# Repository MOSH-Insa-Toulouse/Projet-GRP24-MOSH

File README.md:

# Projet Capteur Graphite GRP24

Ce Git contient les ressources nécessaire pour le projet 2021 qui s'inscrit dans l'UF *"Du capteur au banc de Test"* de l'INSA de Toulouse, 4ème année de Génie Physique.

## Sommaire

---

- [Livrables](##Livrables)
- [Description](##Description)
- [Arduino](##Arduino)
  - [Bibliothèques](###Bibliotèques)
  - [Notre code Arduino](###Notre-Code-Arduino)
- [KICAD](##Projet-KICAD)
  - [Placement des composants](###Placement-des-composants)
  - [Sockets KICAD pour les différents composants](###Sockets-KICAD-pour-les-différents-composants)
- [Application Android apk](##Application-Android-apk)
  - [MIT App Inventor](###MIT-App-Inventor)
  - [Notre application](###Notre-Application)
- [Banc de test](##Banc-de-test)
- [Pistes de réflexion](##Pistes-de-réflexion)
- [Information sur les auteurs](##Information-sur-les-auteurs)

## Livrables

---

- Shield PCB
- Code Arduino permettant la mesure de la resistance R et la tension, ainsi que le contrôle des fonctionnalités BT, OLED et capteur rotatoire
- Application android APK réalisée avec MIT APP INVENTOR
- Datasheet du capteur de déformation

## Description

---
Dans le cadre de l'UF MOSH, nous avons conçu un capteur résistif composé de matériaux peu chers, en effet, un simple papier et un crayon nous permettent de créer ce capteur.
Ici, le phénomène physique est l'effet tunnel, en effet, il existe un lien entre la conduction des électrons et la distance interatopique du réseau percolet.
En faisant varier la distance séparant les particules du réeau (en pliant une feuille de papier sur laquelle on aura déposé du graphite par exemple), la conductivité du graphite varie, la résistivité varier également, et donc, la résistance variera aussi en fonction des dimensions du capteur, c'est cette propriété que l'on va exmploiter avec de créer notre capteur résistif. Nous avons également implémenté  un shield sur notre chaine de mesures, ce dernier a été conçu a l'aide du logiciel KICAD et aura un rôle de conditionneur du signal; le shield est composé d'un module Bluetooth, un écran OLED, un encodeur rotatoire,  un amplificateur transimpédance ainsi qu'une entrée analogique pour le capteur résistif; pour finir, nous avons effectué l'ensemble des tests du circuit sur le logiciel LTSpice.

Nous avons ensuite imprimé notre circuit PCB après validation de l'équipe pedagogique, on a utilisé une carte Arduino pour la lecture des mesures et la création des fonctions relatives à l'écran OLED, au module Bluetooth ainsi qu'a l'encodeur rotatoire même si on n'a pas fini de coder cette partie; avec le site MIT App Inventor, nous avons développé une application Android qui a pour but d'envoyer et de recevoir des donnérs via Bluetooth.
Pour tester notre capteur, nous avons utilisé différents types de crayons (B, HB, 2H), nous avons utilité le banc de test mis a disposition en salle d'instrumentation comportant 7 bosses de rayon de courbure différent, les mesures ont été lues directement sur l'écran OLED.

### Code Arduino

Le code Arduino permet d'afficher les valeurs de tension dans la console ainsi que les valeurs de résistance, nous avons implémenté dans le code arduino le calcul de résistance qui été déjà présent dans l'APK android, le code nous fourni également la valeur de tension lue en sortie du circuit transimpédance, il écrit également la valeur de résistance sur l'écran OLED

### KICAD

Sur le logiciel KICAD on a créé les modèles pour l'écran OLED, le module Bluetooth ainsi que l'encodeur rotatoire, il y a également une interface de notre capteur résistif en graphite.

### Application apk

L'application android permet de lire la valeur de tension, elle calcule également la résistance du capteur en connaissance toutes les valeurs des résistances du circuit transimpédance, elle dessine une courbe représentant la variation de tension sur toute la durée d'utilisation du capteur.

## Arduino
---
En résumé, notre code Arduino permet la mesure d'une tension en sortie du circuit transimpédance, d'envoyer la mesure de cette tension par Bluetooth, le code permet le calcul de la résistancede notre capteur résistif, il envoie également cette valeur par Bluetooth, il affiche la valeur de tension dans la console ainsi que la valeur de résistance sur l'écran OLED, n'ayant pas fini le code de l'encodeur rotatoire, toutes les mesures ont été réalisées sans celui-ci.

### Bibliotèques

- Installer la bibliothèque ["Adafruit GFX Library"](https://github.com/MOSH-Insa-Toulouse/Projet-GRP24-MOSH/blob/main/Libraries%20ajout%C3%A9es/Adafruit-GFX-Library-master.zip)
- Installer la bibliothèque ["Adafruit SSD1306"](https://github.com/MOSH-Insa-Toulouse/Projet-GRP24-MOSH/blob/main/Libraries%20ajout%C3%A9es/Adafruit_SSD1306-master.zip)
- Installer la bibliothèque ["Adafruit BusIOa"](https://github.com/MOSH-Insa-Toulouse/Projet-GRP24-MOSH/blob/main/Libraries%20ajout%C3%A9es/Adafruit_BusIO-master.zip)

### Notre code arduino

Notre code Arduino permet de:

- Mesure la tension de sortie du circuit transimpédance
- Calcule la résistance du capteur de graphite connaissant la fonction de transfert du conditionneur
- Envoie la mesure de la tension et de la resistance via Bluetooth sur 1 octet
- Affiche les mesures de tension, de résistance et possède un menu pour choisir entre un offset et un gain numérique sur un écran OLED
- Gère l'encodeur rotatoire

[_Pour télécharger le code_](https://github.com/MOSH-Insa-Toulouse/Projet-GRP24-MOSH/blob/main/code/code_avec_encodeur_et_gain_non_fini.ino)

[_Pour télécharger la version pour les mesures(sans encodeur rotatoire)_](https://github.com/MOSH-Insa-Toulouse/Projet-GRP24-MOSH/blob/main/code/code_banc_test.ino)

```C++
//connexion BT
#include <SoftwareSerial.h>
#define rxPin 10 //cable jaune sur Tx
#define txPin 11 //cable vert sur Rx
#define baudrate 9600
SoftwareSerial mySerial(rxPin,txPin);

volatile byte RX = 0;
byte serialRX;
byte serialTX;
int action=0;

//OLED (définition)
#include <Adafruit_BusIO_Register.h>
#include <Adafruit_I2CDevice.h>
#include <Adafruit_I2CRegister.h>
#include <Adafruit_SPIDevice.h>

#include <Adafruit_SSD1306.h>
#include <Adafruit_GFX.h>
#include <SPI.h>
#include <Wire.h>

#define oled Adafruit_SSD1306
#define SCREEN_WIDTH 128 // OLED display width, in pixels
#define SCREEN_HEIGHT 32 // OLED display height, in pixels
#define OLED_RESET     4 // Reset pin # (or -1 if sharing Arduino reset pin)

#define SCREEN_ADDRESS 0x3C ///< See datasheet for Address; 0x3C for 128x32
oled display(-1);

//Encodeur (définition)
boolean menu = true; //menu 
#define PinSW 2 // SWITCHS
#define PinCLK 4 //CLK OUTPUT
#define PinDT 3 //DT OUTPUT

volatile boolean TurnDetected;
volatile boolean up;
static long virtualPosition=0; //Position Gain    
 
//gestion des valeurs de tension
#define A0 0
int valeur=0;
int R1=100000;
int R3=100000;
int R2=1000;
int R5=10000;
int Vcc=5;

// detection de transition rotatoire
void ISR ()  {                    //Interrupt Service Routine
 if (digitalRead(PinCLK))
   up = digitalRead(PinDT);
 else
   up = !digitalRead(PinDT);
 TurnDetected = true;
}

void setup() {
  Serial.begin(9600);
  display.begin(SSD1306_SWITCHCAPVCC, SCREEN_ADDRESS); //initialisation OLED

  pinMode(rxPin,INPUT);
  pinMode(txPin,OUTPUT);
  mySerial.begin(9600);

  // test l'affichage correct de l'Oled
 display.clearDisplay();
 display.setTextSize(1);
 display.setTextColor(WHITE);
 display.setCursor(25,15);
 display.println("Projet capteur");
 display.display();
 delay(100);
//pin encoder rotatoire
 pinMode(PinCLK,INPUT);
 pinMode(PinDT,INPUT);  
 pinMode(PinSW,INPUT);
 attachInterrupt (0,ISR,RISING); 
}

//lecture de la valeur sur l'arduino
float lectureValeur () {
  valeur=analogRead(A0);
  return valeur;
  }
//Affichage OLED
void affichage_resistance (float valeur) {
 display.clearDisplay();
 display.setTextSize(1);
 display.setTextColor(WHITE);
 display.setCursor(30,8);
 display.print("valeur res =");
 display.setCursor(30,18);
 float val_res=(1+(R3/R2))*R1*(Vcc/((5*valeur)/1024))-R1-R5; // calcul de la valeur de résistance
 display.print(val_res); //Affichage de la valeur de la résistance
 display.println(" Ohm");
 display.display();
 }

void loop() {
  while (mySerial.available()) {
      
      byte val = map(lectureValeur(), 0, 1024, 0, 255); // conversion 1024/255
  
      mySerial.write(val);

      Serial.println(val);//données envoyées au port

      mySerial.print(",");//données bluetooth
      affichage_resistance(val*4);
  
      sensorValue =   sensorValue * (1+virtualPosition*0.1) //Calcul du Gain

       // Le pushbutton est-il appuyé ?
      if (!(digitalRead(PinSW))) { 
        menu= !menu;
      }

  //modification du gain
      if (TurnDetected)  { 
        if (menu){ 
          if (up  )
        virtualPosition++;
          else
        virtualPosition--;
      }
    TurnDetected = false;

    delay(50);
}
 ```

## Projet KICAD

---
Le projet sur le logiciel KICAD permet de:

- Manipuler le PCB sous forme de Shield pour carte Arduino UNO
- Interfacer capteur graphite via un circuit transimpédance
- Interfacer un module Bluetooth
- Interfacer un écran oled
- Interfacer un encodeur rotatoire

Projet KICAD avec fichiers formats pdf et format GERBER à télécharger [_ici_](https://github.com/MOSH-Insa-Toulouse/Projet-GRP24-MOSH/tree/main/kicad)

### Image du fichier LT SPICE

_Aperçu du Shield PCB (empreinte GERBER)_

### Représentation électrique des composants principaux

### Placement des composants

### Sockets KICAD pour les différents composants

- Amplificateur transimpédance

- Module Blueetooth

- Encodeur rotatoire

## Application Android apk

---
L'application android développée sur MIT App Inventor sert à:

- Récupérer la mesure de tension
- Calcule et affiche la valeur de la résistance du capteur de graphite connaissant la fonction de transfert du conditionneur (en MΩ)
- Trace un graphique qui décrit l'évolution de la mesure de tension au cours du temps

### MIT App inventor

Le site internet de création d'application [_MIT App Inventor_](https://appinventor.mit.edu/)

### Notre application

Notre code de l'application (format .aia) est à télécharger [_ici_](https://github.com/MOSH-Insa-Toulouse/Projet-GRP24-MOSH/blob/main/APK/Capteur_graph.aia)

Notre code de l'application (format .apk) est à télécharger [_ici_](https://github.com/MOSH-Insa-Toulouse/Projet-GRP24-MOSH/blob/main/APK/Capteur_graph.apk)

## Banc de test

---
Afin de tracer les courbes caractéristiques, on a mesuré la résistance du papier a l’aide d’un objet avec 7 « ponts » de différents rayons de courbure, on a déposé le capteur en papier dessus en faisant attention à reproduire à chaque mesure la même expérience et en déposant le papier au même endroit.. Les résultats sont dans notre [_datasheet_](https://github.com/MOSH-Insa-Toulouse/Projet-GRP24-MOSH/blob/main/Datasheet.pdf)

_Image du banc de test_

## Pistes de réflexion

---

- Changer le banc de test car les mesures étaient souvent pas très précises et cela nous a demandé de faire plusieurs capteurs différents afin d'obtenir des résultats satisfaisants.

- Finaliser le code de l'encodeur rotatoire(les résultats de mesure sont fait sans la partie encodeur rotatoire)

- Tester et caractériser plus de capteurs (plus de pistes en graphites avec des différents types de crayons à papier)

## Information sur les auteurs

---
Valentin MORIN / Fayçal HOUSSAINI / François THULLIER

- morin.vltn@gmail.com
- houssain@etud.insa-toulouse.fr
- francois.thullier98@gmail.com 

Étudiants à l'INSA de Toulouse en 4ème année Génie Physique

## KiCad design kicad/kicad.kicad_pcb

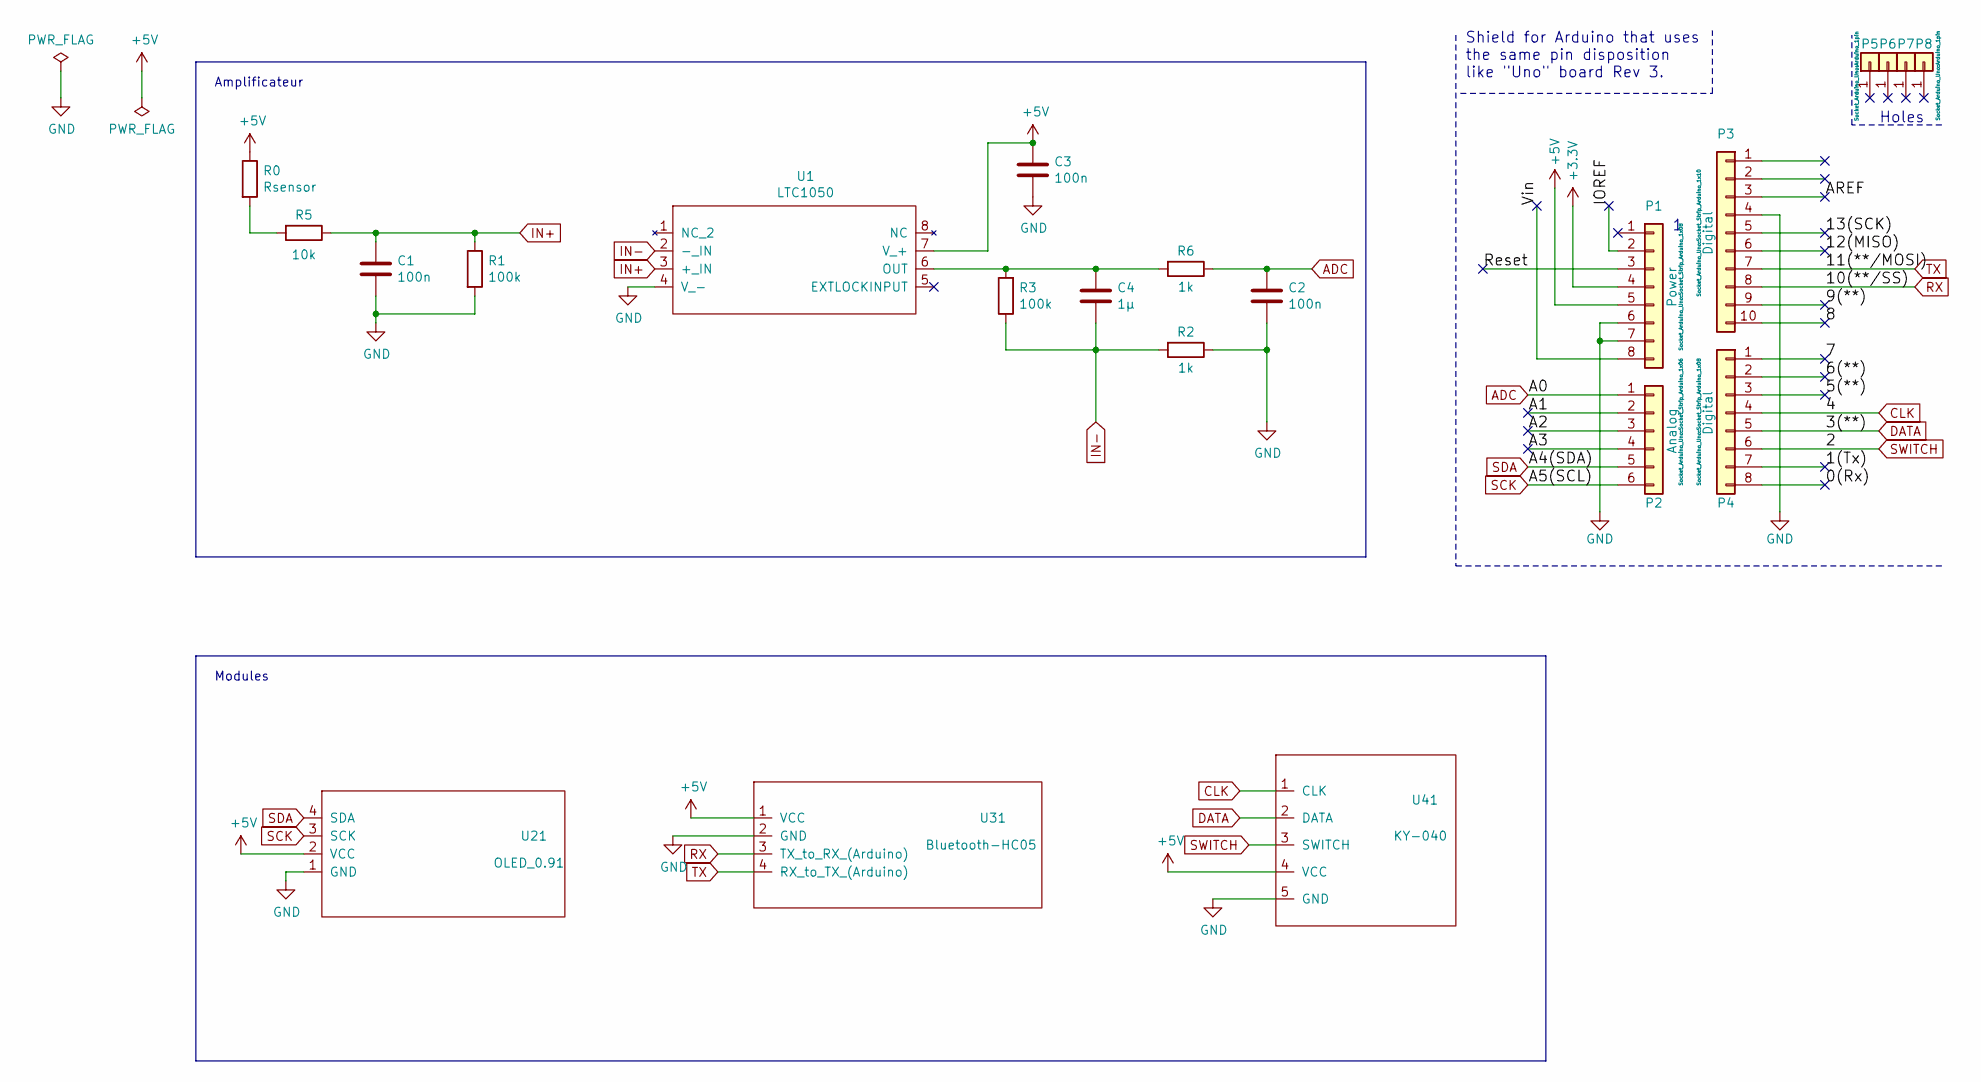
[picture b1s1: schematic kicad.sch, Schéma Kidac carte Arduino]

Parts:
C1, C2, C3: 100n; C_Disc_D3.0mm_W1.6mm_P2.50mm
C4: 1µ; C_Axial_L5.1mm_D3.1mm_P7.50mm_Horizontal
P1: Power; Socket_Strip_Arduino_1x08
P2: Analog; Socket_Strip_Arduino_1x06
P3: Digital; Socket_Strip_Arduino_1x10
P4: Digital; Socket_Strip_Arduino_1x08
P5, P6, P7, P8: CONN_01X01; Arduino_1pin
R0: Rsensor; R_Axial_DIN0309_L9.0mm_D3.2mm_P12.70mm_Horizontal
R1, R3: 100k; R_Axial_DIN0309_L9.0mm_D3.2mm_P12.70mm_Horizontal
R2, R6: 1k; R_Axial_DIN0309_L9.0mm_D3.2mm_P12.70mm_Horizontal
R5: 10k; R_Axial_DIN0309_L9.0mm_D3.2mm_P12.70mm_Horizontal
U1: LTC1050; LTC
U21: OLED_0.91; OLED
U31: Bluetooth-HC05; HC05
U41: KY-040; KY

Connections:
+3V3: P1.4
+5V: C3.1, P1.5, R0.1, U1.7 (V_+), U21.2 (VCC), U31.1 (VCC), U41.4 (VCC)
/0(Rx): P4.8
/1(Tx): P4.7
/5(**): P4.3
/6(**): P4.2
/7: P4.1
/8: P3.10
/9(**): P3.9
/12(MISO): P3.6
/13(SCK): P3.5
/A1: P2.2
/A2: P2.3
/A3: P2.4
/AREF: P3.3
/IOREF: P1.2
/Reset: P1.3
/Vin: P1.8
ADC: C2.1, P2.1, R6.1
CLK: P4.4, U41.1 (CLK)
DATA: P4.5, U41.2 (DATA)
GND: C1.2, C2.2, C3.2, P1.6, P1.7, P3.4, R1.2, R2.1, U1.4 (V_-), U21.1 (GND), U31.2 (GND), U41.5 (GND)
IN+: C1.1, R1.1, R5.1, U1.3 (+_IN)
IN-: C4.2, R2.2, R3.1, U1.2 (-_IN)
unnamed: C4.1, R3.2, R6.2, U1.6 (OUT)
unnamed: R0.2, R5.2
RX: P3.8, U31.3 (TX_to_RX_(Arduino))
SCK: P2.6, U21.3 (SCK)
SDA: P2.5, U21.4 (SDA)
SWITCH: P4.6, U41.3 (SWITCH)
TX: P3.7, U31.4 (RX_to_TX_(Arduino))

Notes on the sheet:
Holes
Shield for Arduino that uses the same pin disposition like "Uno" board Rev 3.
Amplificateur
Modules

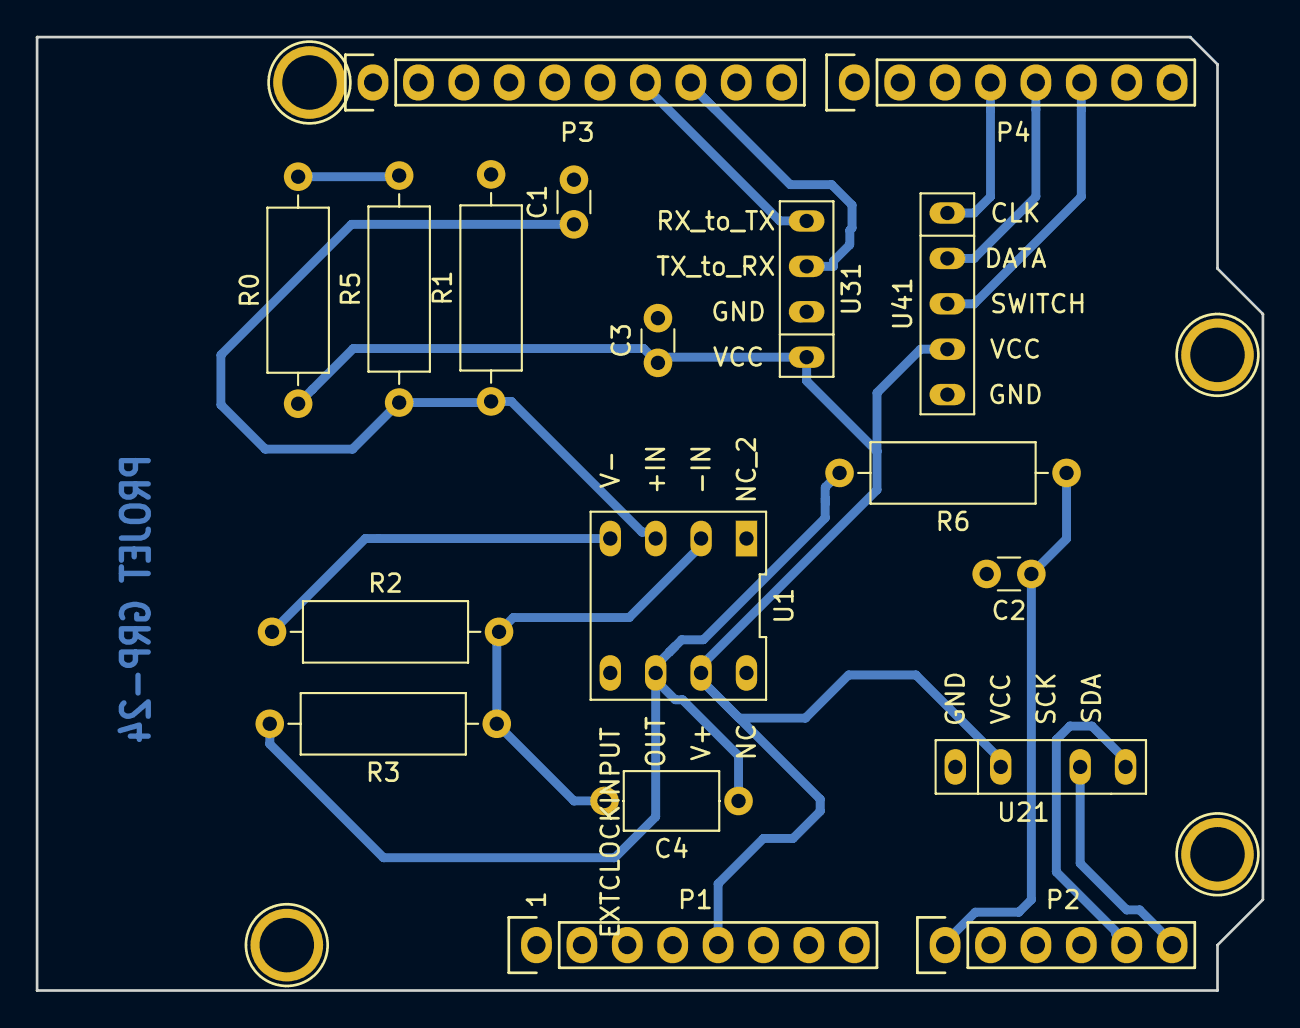
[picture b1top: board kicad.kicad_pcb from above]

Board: 2 copper layers, 68.6 x 53.3 mm, 22 parts (0 on the bottom side), 14 nets.

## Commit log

2021-05-04 Rename code.ino to code_banc_test.ino
